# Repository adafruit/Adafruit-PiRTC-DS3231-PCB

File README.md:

## Adafruit PiRTC Precise DS3231 Real Time Clock for Raspberry Pi PCB

<a href="http://www.adafruit.com/products/4282"><br/>
Click here to purchase one from the Adafruit shop</a>

PCB files for the Adafruit PiRTC Precise DS3231 Real Time Clock for Raspberry Pi. 

Format is EagleCAD schematic and board layout
* https://www.adafruit.com/product/4282

### Description

This is the best battery-backed real time clock (RTC) you can get that allows your Raspberry Pi project to keep track of time if the power is lost. Perfect for data-logging, clock-building, NTP servers, time-stamping, timers and alarms, etc. Equipped with a genuine DS3231 RTC, it works great with the Raspberry Pi and has native kernel support.

The datasheet for the DS3231 explains that this part is an "Extremely Accurate I²C-Integrated RTC/TCXO/Crystal". And, hey, it does exactly what it says on the tin! This Real Time Clock (RTC) is the most precise you can get in a small, low power package.

Most RTCs use an external 32kHz timing crystal that is used to keep time with low current draw. And that's all well and good, but those crystals have slight drift, particularly when the temperature changes (the temperature changes the oscillation frequency very very very slightly but it does add up!) This RTC is in a beefy package because the crystal is inside the chip! And right next to the integrated crystal is a temperature sensor. That sensor compensates for the frequency changes by adding or removing clock ticks so that the timekeeping stays on schedule.

Many "cheap" DS3231 RTC boards do not use genuine Maxim DS3231's - you'll get a non-calibrated RTC which does not maintain the timekeeping quality that is specified! We purchase these DS3231's from Maxim direct so we know they are 100% genuine.

Works perfectly with any Raspberry Pi (or similar single board linux computer) including the Pi 1, Pi 2, Pi 3, Pi 4, Pi Zero, A+, B+ etc.

* Fully assembled & tested PCB plugs directly into your Pi's GPIO pins - No soldering required!
* Will keep time for 5 years or more

Note: This product does not come with a CR1220 coin cell battery. We recommend you purchase a coin cell battery to use with this product.

### License

Adafruit invests time and resources providing this open source design, please support Adafruit and open-source hardware by purchasing products from [Adafruit](https://www.adafruit.com)!

Designed by Limor Fried/Ladyada for Adafruit Industries.

Creative Commons Attribution/Share-Alike, all text above must be included in any redistribution. 
See license.txt for additional details.

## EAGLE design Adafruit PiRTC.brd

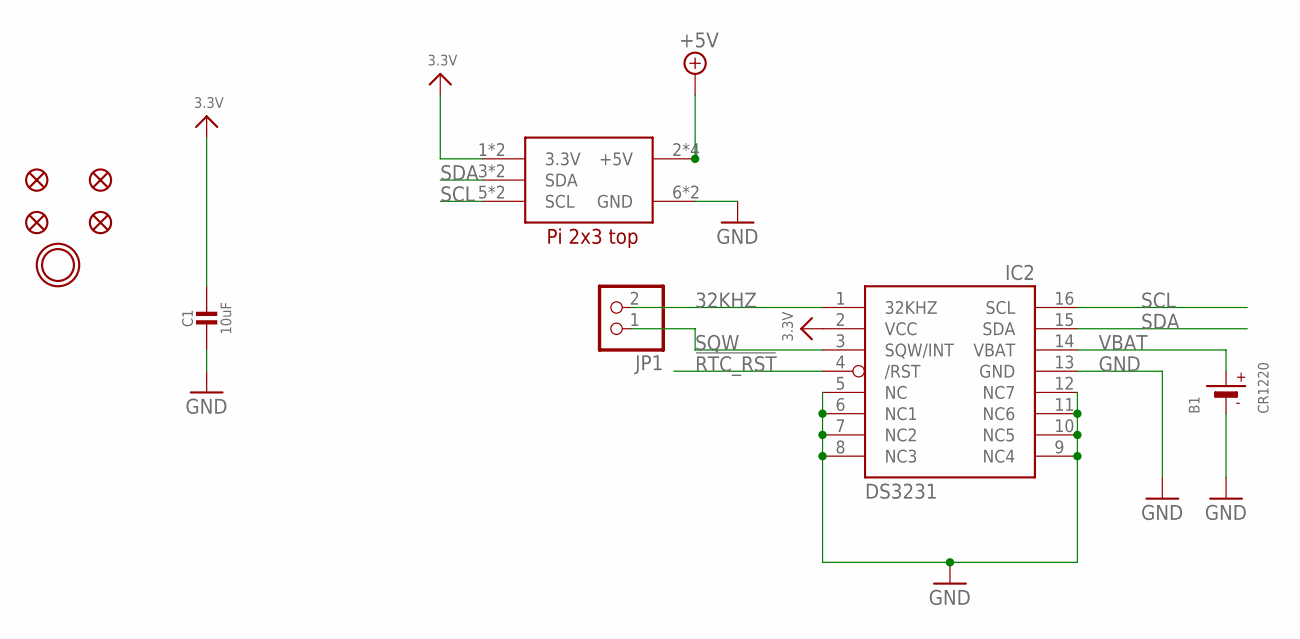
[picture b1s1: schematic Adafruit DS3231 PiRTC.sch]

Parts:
B1: CR1220
C1: 10uF; 0805-NO
FID1, FID2, FID3, FID4: FIDUCIAL_1MM
IC2: DS3231/SO; SO16W
JP1: HEADER-1X2ROUND; 1X02_ROUND
RPI1: RASPBERRYPI_2X3; RASPBERRYPI_2X3_THMSMT
U$4: MOUNTINGHOLE3.0THIN; MOUNTINGHOLE_3.0_PLATEDTHIN

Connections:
3.3V: C1.1, IC2.2 (VCC), RPI1.1 (3.3V), RPI1.1' (3.3V)
32KHZ: IC2.1 (32KHZ), JP1.2
!RTC_RST: IC2.4 (/RST)
+5V: RPI1.2 (+5V), RPI1.2' (+5V), RPI1.4 (+5V), RPI1.4' (+5V)
GND: B1.-, C1.2, IC2.5 (NC), IC2.6 (NC1), IC2.7 (NC2), IC2.8 (NC3), IC2.9 (NC4), IC2.10 (NC5), IC2.11 (NC6), IC2.12 (NC7), IC2.13 (GND), RPI1.6 (GND), RPI1.6' (GND)
SCL: IC2.16 (SCL), RPI1.5 (SCL), RPI1.5' (SCL)
SDA: IC2.15 (SDA), RPI1.3 (SDA), RPI1.3' (SDA)
SQW: IC2.3 (SQW/INT), JP1.1
VBAT: B1.+$1 (+), B1.+$2 (+), IC2.14 (VBAT)

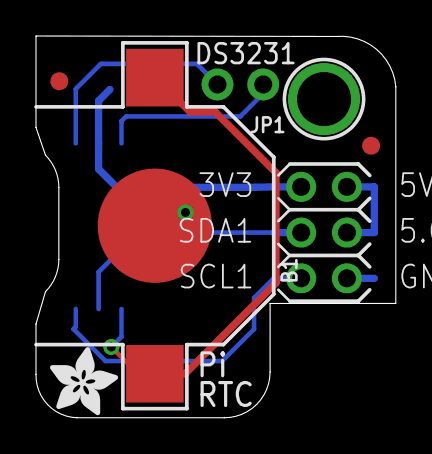
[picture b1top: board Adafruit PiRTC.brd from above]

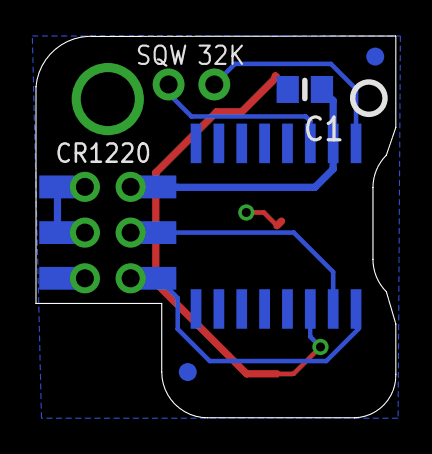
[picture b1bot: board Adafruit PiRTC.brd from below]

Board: 2 copper layers, 20.0 x 21.2 mm, 12 parts (5 on the bottom side), 8 nets.

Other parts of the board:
U$2: ADAFRUIT_3.5MM
U$3: PCBFEAT-REV-040

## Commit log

2021-02-22 Adding board files.
2021-02-22 Update board files.

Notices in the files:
parts and their libraries:
microbuilder: This work is placed in the public domain, and may be freely used for commercial and non-commercial work with the following conditions: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
